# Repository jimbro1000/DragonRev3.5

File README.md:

# DRAGON 32 CPU Rev 3(.5) #

This project contains the design for a hugely upgraded version
of the Dragon 32 (technically a Dragon 64 for pedants)

The basis of the design is the Dragon 32 recreation that I have
been refining for some time. The peripheral IO remains as originally
specified by Dragon Data but the ram, address multiplexer and video
display generator or implemented on a separate plug-in component.

Technically the original ICs could be implemented on the plug-in and
you would be left with an original piece of hardware (in terms of
function). I already have a board for that though...

The benefit of the plugin board is to implement the complex (and
expensive) fabrication on a smaller device and abstract away the
upgrades that are contained.

Almost every passive component and supporting logic ICs have been
switched to surface mount technology. This means the board can be
part assembled at relatively low cost, leaving just the major ICs,
ports, connectors and relay to be hand assembled.

## Core Design ##
### Main Board ###

The main board replicates the footprint of the original D64 PCB.
Ports and fixings are all in their original positions.

The CPU lives on the main board with any speed variant supported
including the HD63C09. The onboard ROM is integrated into a single 
chip holding both banks of the D64 ROM image.

All IO (except video) is performed by the original hardware so the 
two PIAs and UART are retained.

The device select signals for peripherals has been disambiguated
from two devices which repeat the same four addresses eight times, 
to sixteen devices, each with four mapped addresses.

* $FF00-$FF03 (P0a) is still the original PIA0
* $FF04-$FF07 (P0b) is the original UART
* $FF20-$FF23 (P1a) is still the original PIA1

These three blocks maintain compatibility with the original ROM
software.

The other blocks (P0c-P0g and P1b-P1g) are unused and can be
adopted for other hardware (see audio)

### Core Board ###

The core board provides RAM, Video and SAM functionality. The
minimum version of this would be the original RAM, VDG and SAM
chips which effectively reproduces the original D64 specification.

At this time two upgrade core boards exist. The first is a mild
upgrade that provides 2MB of RAM, a SAMx implementation and an
upgraded VDG that replicates the video functionality of the 
CoCo3 GIME chip

The second core board provides all of the capabilities of the
first board but adds a soft 6809 CPU that can operate alongside
or instead of the CPU on the main board. This second CPU can
operate at much higher speeds than the original, match the
speed of the original or be completely disabled. When both
CPUs are operating the second CPU can be completely detached
from everything except RAM and running on an independent
clock cycle, or it can share the full bus with the hardware
CPU utilising the bus mastering signals.

The second core also introduces a DMA capability that enables
very fast memory copy actions, running independently of either
CPU.

The video capabilities of the second core add sprite handling
and tile based video modes, all in a layered video system that
allows tiles, bitmaps and sprites to exist on the same display.

For details of the core implementations see the separate
hardware and firmware repositories.

### Audio Board ###

The main board will (but does not currently) provide a socket
for an audio upgrade. The proposal is to utilise four or six
peripheral address blocks to provide an interface to the audio
board. Each block effectively represents a single audio device.

The multi device approach should allow the audio board to 
generate a rich stereo output with multiple audio waveforms
per stereo channel.

Optionally I want to look at live mixing of the audio to allow
user selection of which waveform ends up on which channel. This
would likely consume another peripheral address block.

Following this approach would permit the use of original sound
generator chips but has the problem of identifying the source
of interrupts.

An alternative is to define a soft audio generator in a MCU
or CPLD that focuses all of the IO into a single hardware
device (possibly still using multiple peripheral IO blocks)
but potentially makes the hardware interface non-standard.
If a suitable open source firmware definition can be
identified, this is likely to be the better option.

An example of this would be the [YM2149 PSG System](https://github.com/nockieboy/YM2149_PSG_system)
that implements a simulation of dual YM2149s (or 
AY-3-8910s) with stereo mixer and bass and treble controls.

Due to the limited external IO required this could be implemeted
on a relatively cheap, modest FPGA device rather than the main core
board which requires a significant level of IO connectivity.

## Modifications ##
### Joysticks ###

The two joystick ports provide a second fire button capability
wired to consecutive keyboard rows, as per the Tandy CoCo. 
Unless a two button joystick is used this make no difference to
the operation of the computer. It also requires the use of 6-pin 
DIN sockets, these are pin compatible with the 5-pin originals
so a regular single button joystick can still be used.

The two extra buttons can also be disabled by omitting L3 and L4

## License

This project and all its hardware design are licensed under
creative commons [CC BY-NC 4.0](https://creativecommons.org/licenses/by-nc/4.0/deed.en)

__You are free to:__

Share - copy and redistribute the material in any medium or format

Adapt - remix, transform, and build upon the material

The licensor cannot revoke these freedoms as long as you follow the 
license terms.

__Under the following terms:__

Attribution - You must give appropriate credit, provide a link to the 
license, and indicate if changes were made. You may do so in any 
reasonable manner, but not in any way that suggests the licensor 
endorses you or your use.

NonCommercial - You may not use the material for commercial purposes.

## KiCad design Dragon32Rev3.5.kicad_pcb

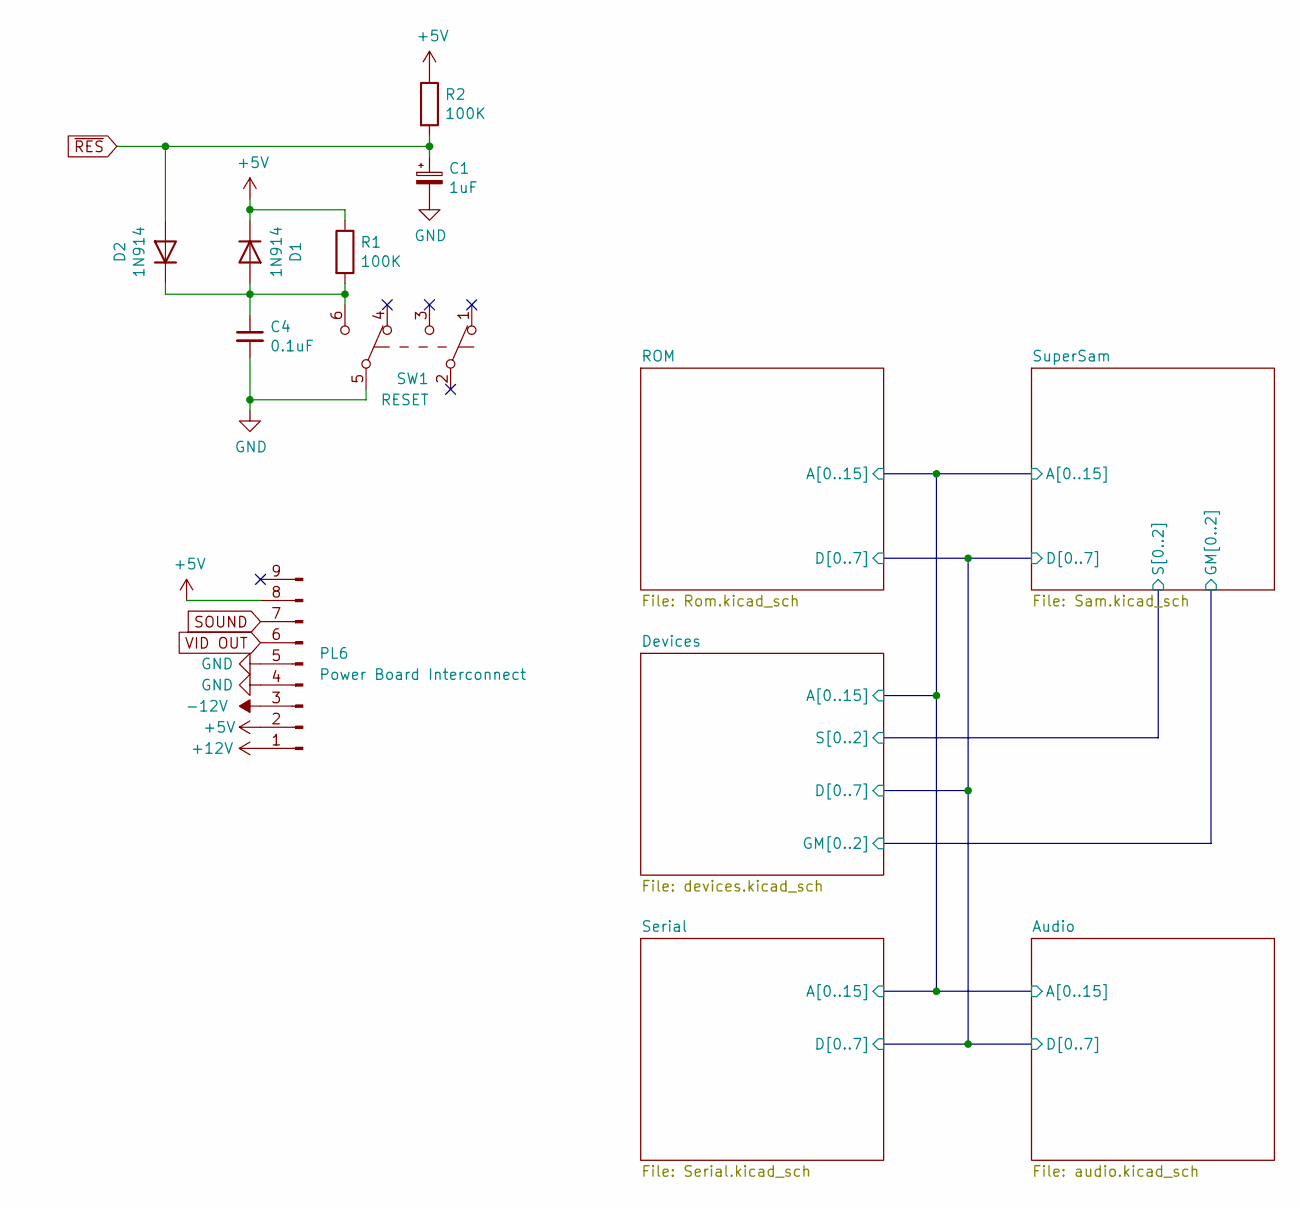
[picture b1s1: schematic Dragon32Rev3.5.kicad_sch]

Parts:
C1: 1uF; CP_Elec_4x4.5; DigiKey 732-8541-1-ND
C4: 0.1uF; C_0805_2012Metric; DigiKey C0805F104K1RACAUTO
D1, D2: 1N914; D_SOD-523; DigiKey 1N914BWTCT-ND
PL6: Power Board Interconnect; Molex_KK-396_A-41791-0009_1x09_P3.96mm_Vertical; DigiKey 2057-LHD-09-TS-ND
R1, R2: 100K; R_0402_1005Metric; DigiKey YAG2304CT-ND
SW1: RESET; Button_AlpsAlpine_SPUN190900; DigiKey 401-1225-ND

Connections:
+5V: D1.1 (K), PL6.2, PL6.8, R1.1, R2.1; also elsewhere on the board
+12V: PL6.1; also elsewhere on the board
-12V: PL6.3; also elsewhere on the board
GND: C1.2, C4.2, PL6.4, PL6.5, SW1.5 (B); also elsewhere on the board
unnamed: C4.1, D1.2 (A), D2.1 (K), R1.2, SW1.6 (C)
SOUND: PL6.7; also elsewhere on the board
VID OUT: PL6.6; also elsewhere on the board
~RES: C1.1, D2.2 (A), R2.2

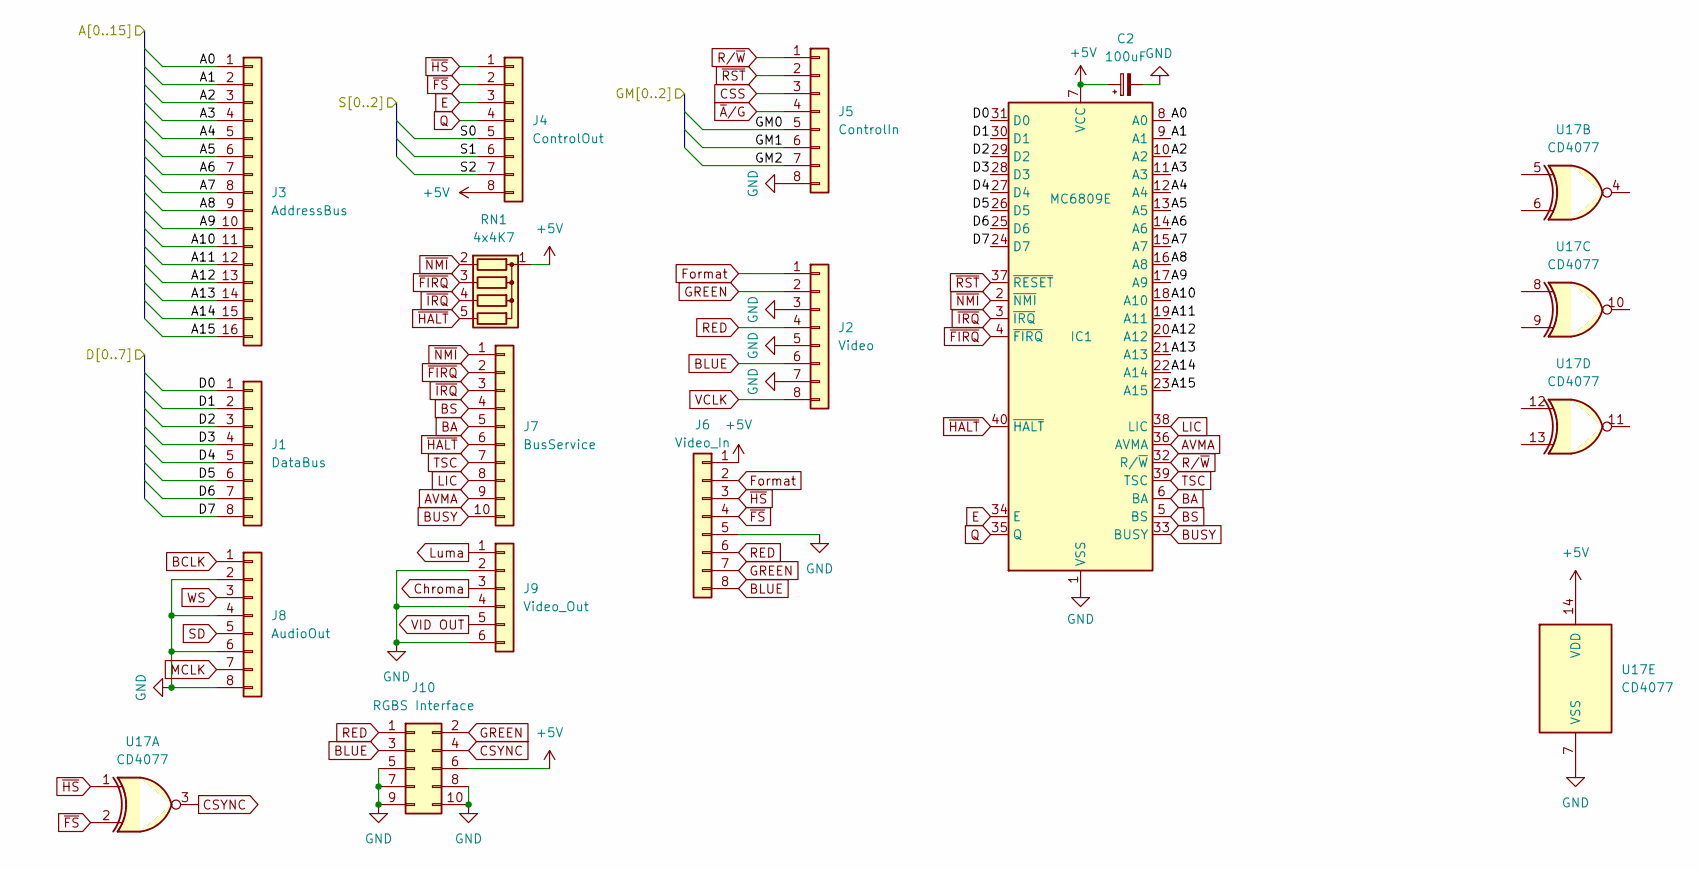
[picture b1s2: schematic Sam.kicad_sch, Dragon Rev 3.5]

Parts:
C2: 100uF; CP_Elec_5x5.3; DigiKey 732-6410-1-ND
IC1: MC6809E; DIP-40_W15.24mm; Mouser 517-4840-6000-CP
J1: DataBus; PinHeader_1x08_P2.54mm_Vertical
J2: Video; PinHeader_1x08_P2.54mm_Vertical
J3: AddressBus; PinHeader_1x16_P2.54mm_Vertical
J4: ControlOut; PinHeader_1x08_P2.54mm_Vertical
J5: ControlIn; PinHeader_1x08_P2.54mm_Vertical
J6: Video_In; PinHeader_1x08_P2.54mm_Vertical
J7: BusService; PinHeader_1x10_P2.54mm_Vertical
J8: AudioOut; PinHeader_1x08_P2.54mm_Vertical
J9: Video_Out; PinHeader_1x06_P2.54mm_Vertical
J10: RGBS Interface; IDC-Header_2x05_P2.54mm_Vertical
RN1: 4x4K7; R_Array_SIP5
U17: CD4077; SOIC-16_3.9x9.9mm_P1.27mm; DigiKey 296-31521-1-ND

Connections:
+5V: C2.1, IC1.7 (VCC), J4.8, J6.1, J10.6, RN1.1 (common), U17.14 (VDD); also elsewhere on the board
/Audio/A0: IC1.8 (A0), J3.1; also elsewhere on the board
/Audio/A1: IC1.9 (A1), J3.2; also elsewhere on the board
/Audio/A2: IC1.10 (A2), J3.3; also elsewhere on the board
/Audio/A3: IC1.11 (A3), J3.4; also elsewhere on the board
/Audio/A4: IC1.12 (A4), J3.5; also elsewhere on the board
/Audio/A5: IC1.13 (A5), J3.6; also elsewhere on the board
/Audio/A6: IC1.14 (A6), J3.7; also elsewhere on the board
/Audio/A7: IC1.15 (A7), J3.8; also elsewhere on the board
/Audio/A8: IC1.16 (A8), J3.9; also elsewhere on the board
/Audio/A9: IC1.17 (A9), J3.10; also elsewhere on the board
/Audio/A10: IC1.18 (A10), J3.11; also elsewhere on the board
/Audio/A11: IC1.19 (A11), J3.12; also elsewhere on the board
/Audio/A12: IC1.20 (A12), J3.13; also elsewhere on the board
/Audio/A13: IC1.21 (A13), J3.14; also elsewhere on the board
/Audio/A14: IC1.22 (A14), J3.15; also elsewhere on the board
/Audio/A15: IC1.23 (A15), J3.16; also elsewhere on the board
/Audio/D0: IC1.31 (D0), J1.1; also elsewhere on the board
/Audio/D1: IC1.30 (D1), J1.2; also elsewhere on the board
/Audio/D2: IC1.29 (D2), J1.3; also elsewhere on the board
/Audio/D3: IC1.28 (D3), J1.4; also elsewhere on the board
/Audio/D4: IC1.27 (D4), J1.5; also elsewhere on the board
/Audio/D5: IC1.26 (D5), J1.6; also elsewhere on the board
/Audio/D6: IC1.25 (D6), J1.7; also elsewhere on the board
/Audio/D7: IC1.24 (D7), J1.8; also elsewhere on the board
/Devices/GM0: J5.5; also elsewhere on the board
/Devices/GM1: J5.6; also elsewhere on the board
/Devices/GM2: J5.7; also elsewhere on the board
/Devices/S0: J4.5; also elsewhere on the board
/Devices/S1: J4.6; also elsewhere on the board
/Devices/S2: J4.7; also elsewhere on the board
AVMA: IC1.36 (AVMA), J7.9
BA: IC1.6 (BA), J7.5
BCLK: J8.1; also elsewhere on the board
BLUE: J2.6, J6.8, J10.3
BS: IC1.5 (BS), J7.4
BUSY: IC1.33 (BUSY), J7.10
CSS: J5.3; also elsewhere on the board
CSYNC: J10.4, U17.3
Chroma: J9.3
E: IC1.34 (E), J4.3; also elsewhere on the board
Format: J2.1, J6.2
GND: C2.2, IC1.1 (VSS), J2.3, J2.5, J2.7, J5.8, J6.5, J8.2, J8.4, J8.6, J8.8, J9.2, J9.4, J9.6, J10.5, J10.7, J10.8, J10.9, J10.10, U17.7 (VSS); also elsewhere on the board
GREEN: J2.2, J6.7, J10.2
LIC: IC1.38 (LIC), J7.8
Luma: J9.1
MCLK: J8.7; also elsewhere on the board
Q: IC1.35 (Q), J4.4; also elsewhere on the board
RED: J2.4, J6.6, J10.1
R/~W: IC1.32 (R/~W), J5.1; also elsewhere on the board
SD: J8.5; also elsewhere on the board
TSC: IC1.39 (TSC), J7.7
VCLK: J2.8; also elsewhere on the board
VID OUT: J9.5; also elsewhere on the board
WS: J8.3; also elsewhere on the board
~A/G: J5.4; also elsewhere on the board
~FIRQ: IC1.4 (~FIRQ), J7.2, RN1.3 (R2); also elsewhere on the board
~FS: J4.2, J6.4, U17.2; also elsewhere on the board
~HALT: IC1.40 (~HALT), J7.6, RN1.5 (R4); also elsewhere on the board
~HS: J4.1, J6.3, U17.1
~IRQ: IC1.3 (~IRQ), J7.3, RN1.4 (R3); also elsewhere on the board
~NMI: IC1.2 (~NMI), J7.1, RN1.2 (R1); also elsewhere on the board
~RST: IC1.37 (~RESET), J5.2; also elsewhere on the board

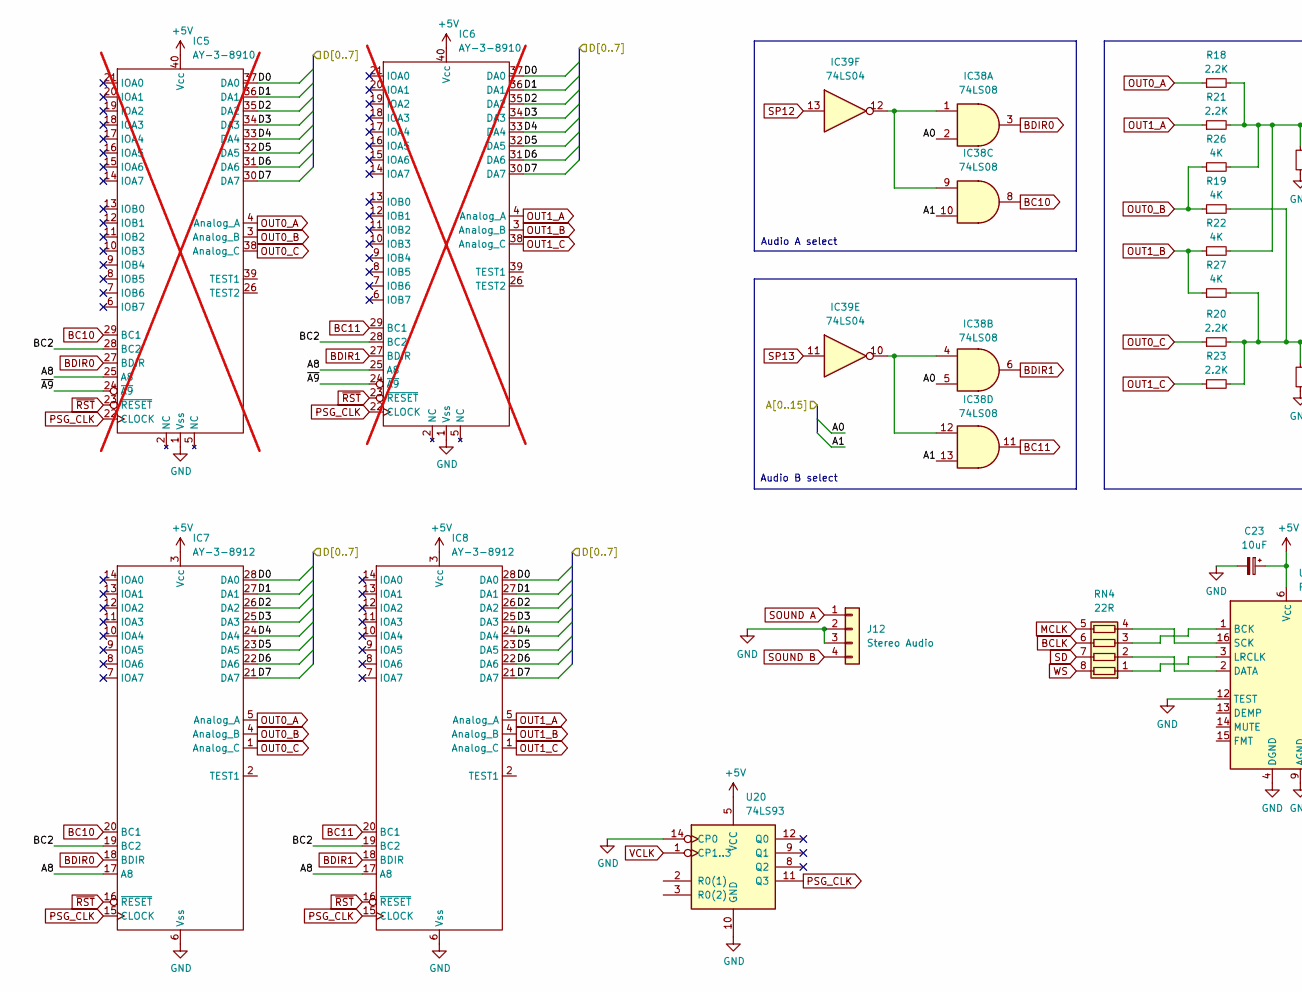
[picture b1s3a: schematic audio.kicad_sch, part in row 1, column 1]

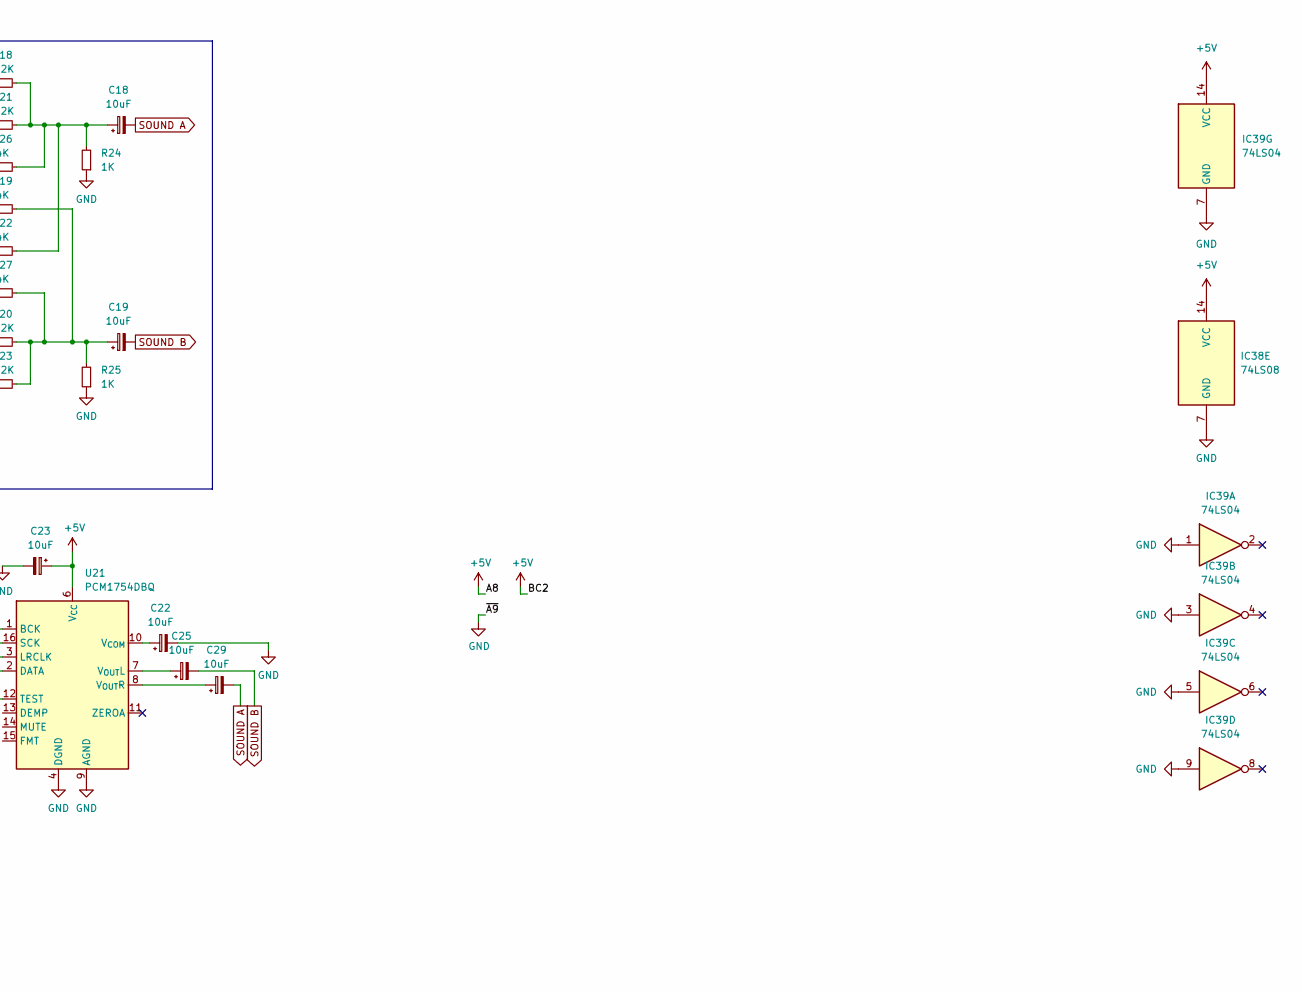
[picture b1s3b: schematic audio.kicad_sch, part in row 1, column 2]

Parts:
C18, C19, C22, C23, C25, C29: 10uF; CP_Elec_4x3
IC5, IC6: AY-3-8910; DIP-40_W15.24mm_Socket; not fitted
IC7, IC8: AY-3-8912; DIP-28_W15.24mm_Socket
IC38: 74LS08; SOIC-14_3.9x8.7mm_P1.27mm; LCSC C22394768
IC39: 74LS04; SOIC-14_3.9x8.7mm_P1.27mm; LCSC C22374093
J12: Stereo Audio; JST_EH_S4B-EH_1x04_P2.50mm_Horizontal
R18, R20, R21, R23: 2.2K; R_0603_1608Metric
R19, R22, R26, R27: 4K; R_0603_1608Metric
R24, R25: 1K; R_0603_1608Metric
RN4: 22R; R_Array_Convex_4x0603
U20: 74LS93; SOIC-14_3.9x8.7mm_P1.27mm
U21: PCM1754DBQ; SSOP-16_3.9x4.9mm_P0.635mm

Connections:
+5V: C23.1, IC5.25 (A8), IC5.28 (BC2), IC5.40 (Vcc), IC6.25 (A8), IC6.28 (BC2), IC6.40 (Vcc), IC7.3 (Vcc), IC7.17 (A8), IC7.19 (BC2), IC8.3 (Vcc), IC8.17 (A8), IC8.19 (BC2), IC38.14 (VCC), IC39.14 (VCC), U20.5 (VCC), U21.6 (V_{CC}); also elsewhere on the board
/Audio/A0: IC38.2, IC38.5; also elsewhere on the board
/Audio/A1: IC38.10, IC38.13; also elsewhere on the board
/Audio/D0: IC5.37 (DA0), IC6.37 (DA0), IC7.28 (DA0), IC8.28 (DA0); also elsewhere on the board
/Audio/D1: IC5.36 (DA1), IC6.36 (DA1), IC7.27 (DA1), IC8.27 (DA1); also elsewhere on the board
/Audio/D2: IC5.35 (DA2), IC6.35 (DA2), IC7.26 (DA2), IC8.26 (DA2); also elsewhere on the board
/Audio/D3: IC5.34 (DA3), IC6.34 (DA3), IC7.25 (DA3), IC8.25 (DA3); also elsewhere on the board
/Audio/D4: IC5.33 (DA4), IC6.33 (DA4), IC7.24 (DA4), IC8.24 (DA4); also elsewhere on the board
/Audio/D5: IC5.32 (DA5), IC6.32 (DA5), IC7.23 (DA5), IC8.23 (DA5); also elsewhere on the board
/Audio/D6: IC5.31 (DA6), IC6.31 (DA6), IC7.22 (DA6), IC8.22 (DA6); also elsewhere on the board
/Audio/D7: IC5.30 (DA7), IC6.30 (DA7), IC7.21 (DA7), IC8.21 (DA7); also elsewhere on the board
BC10: IC5.29 (BC1), IC7.20 (BC1), IC38.8
BC11: IC6.29 (BC1), IC8.20 (BC1), IC38.11
BCLK: RN4.6 (R3.2); also elsewhere on the board
BDIR0: IC5.27 (BDIR), IC7.18 (BDIR), IC38.3
BDIR1: IC6.27 (BDIR), IC8.18 (BDIR), IC38.6
GND: C22.2, C23.2, IC5.1 (Vss), IC5.24 (~A9), IC6.1 (Vss), IC6.24 (~A9), IC7.6 (Vss), IC8.6 (Vss), IC38.7 (GND), IC39.1, IC39.3, IC39.5, IC39.7 (GND), IC39.9, J12.2, J12.3, R24.1, R25.1, U20.10 (GND), U20.14 (CP0), U21.4 (DGND), U21.9 (AGND), U21.12 (TEST); also elsewhere on the board
MCLK: RN4.5 (R4.2); also elsewhere on the board
unnamed: C18.1, R18.2, R21.2, R22.2, R24.2, R26.2
unnamed: C19.1, R19.2, R20.2, R23.2, R25.2, R27.2
unnamed: IC38.1, IC38.9, IC39.12
unnamed: IC38.4, IC38.12, IC39.10
unnamed: RN4.1 (R1.1), U21.3 (LRCLK)
unnamed: RN4.2 (R2.1), U21.2 (DATA)
unnamed: RN4.3 (R3.1), U21.1 (BCK)
unnamed: RN4.4 (R4.1), U21.16 (SCK)
unnamed: C22.1, U21.10 (V_{COM})
unnamed: C25.1, U21.7 (V_{OUT}L)
unnamed: C29.1, U21.8 (V_{OUT}R)
OUT0_A: IC5.4 (Analog_A), IC7.5 (Analog_A), R18.1
OUT0_B: IC5.3 (Analog_B), IC7.4 (Analog_B), R19.1, R26.1
OUT0_C: IC5.38 (Analog_C), IC7.1 (Analog_C), R20.1
OUT1_A: IC6.4 (Analog_A), IC8.5 (Analog_A), R21.1
OUT1_B: IC6.3 (Analog_B), IC8.4 (Analog_B), R22.1, R27.1
OUT1_C: IC6.38 (Analog_C), IC8.1 (Analog_C), R23.1
PSG_CLK: IC5.22 (CLOCK), IC6.22 (CLOCK), IC7.15 (CLOCK), IC8.15 (CLOCK), U20.11 (Q3)
SD: RN4.7 (R2.2); also elsewhere on the board
SOUND A: C18.2, C29.2, J12.1
SOUND B: C19.2, C25.2, J12.4
SP12: IC39.13; also elsewhere on the board
SP13: IC39.11; also elsewhere on the board
VCLK: U20.1 (CP1..3); also elsewhere on the board
WS: RN4.8 (R1.2); also elsewhere on the board
~RST: IC5.23 (~RESET), IC6.23 (~RESET), IC7.16 (~RESET), IC8.16 (~RESET); also elsewhere on the board

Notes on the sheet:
Audio B select
Audio A select

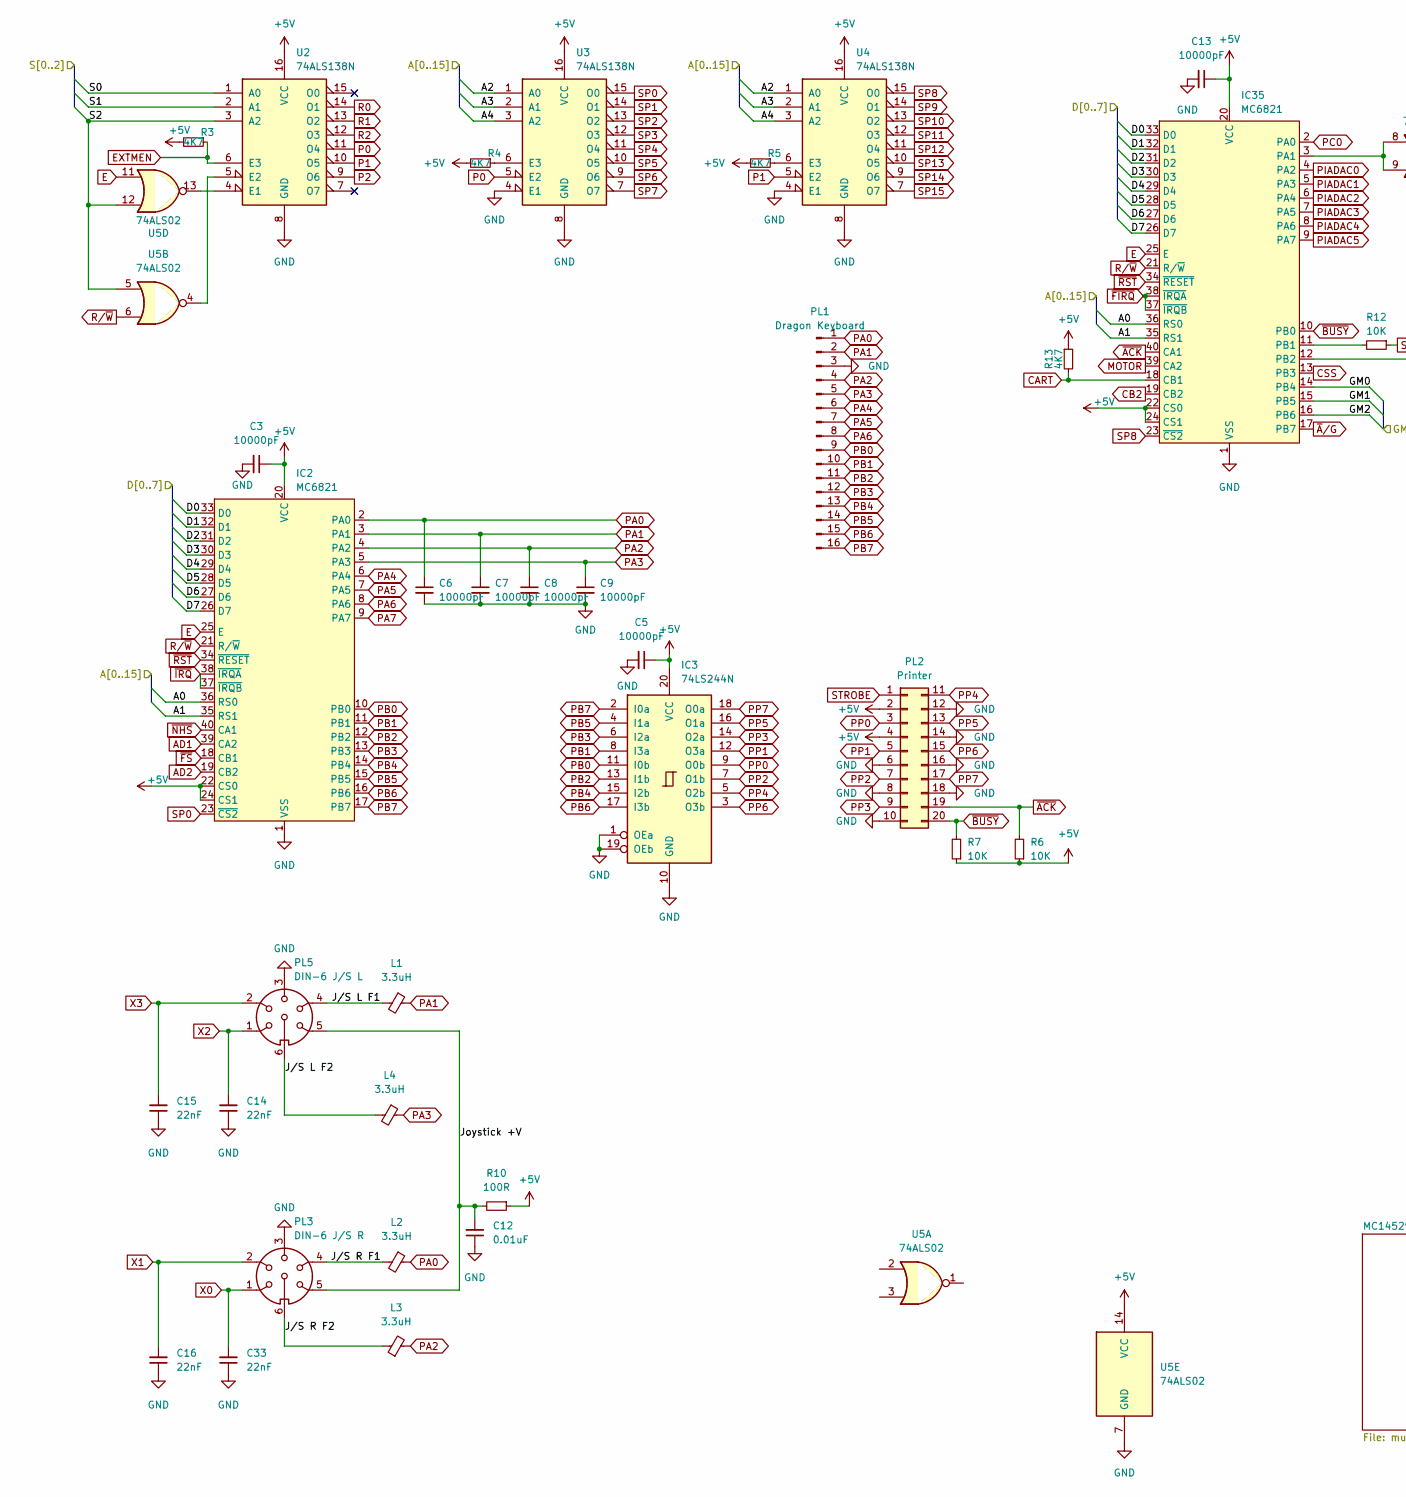
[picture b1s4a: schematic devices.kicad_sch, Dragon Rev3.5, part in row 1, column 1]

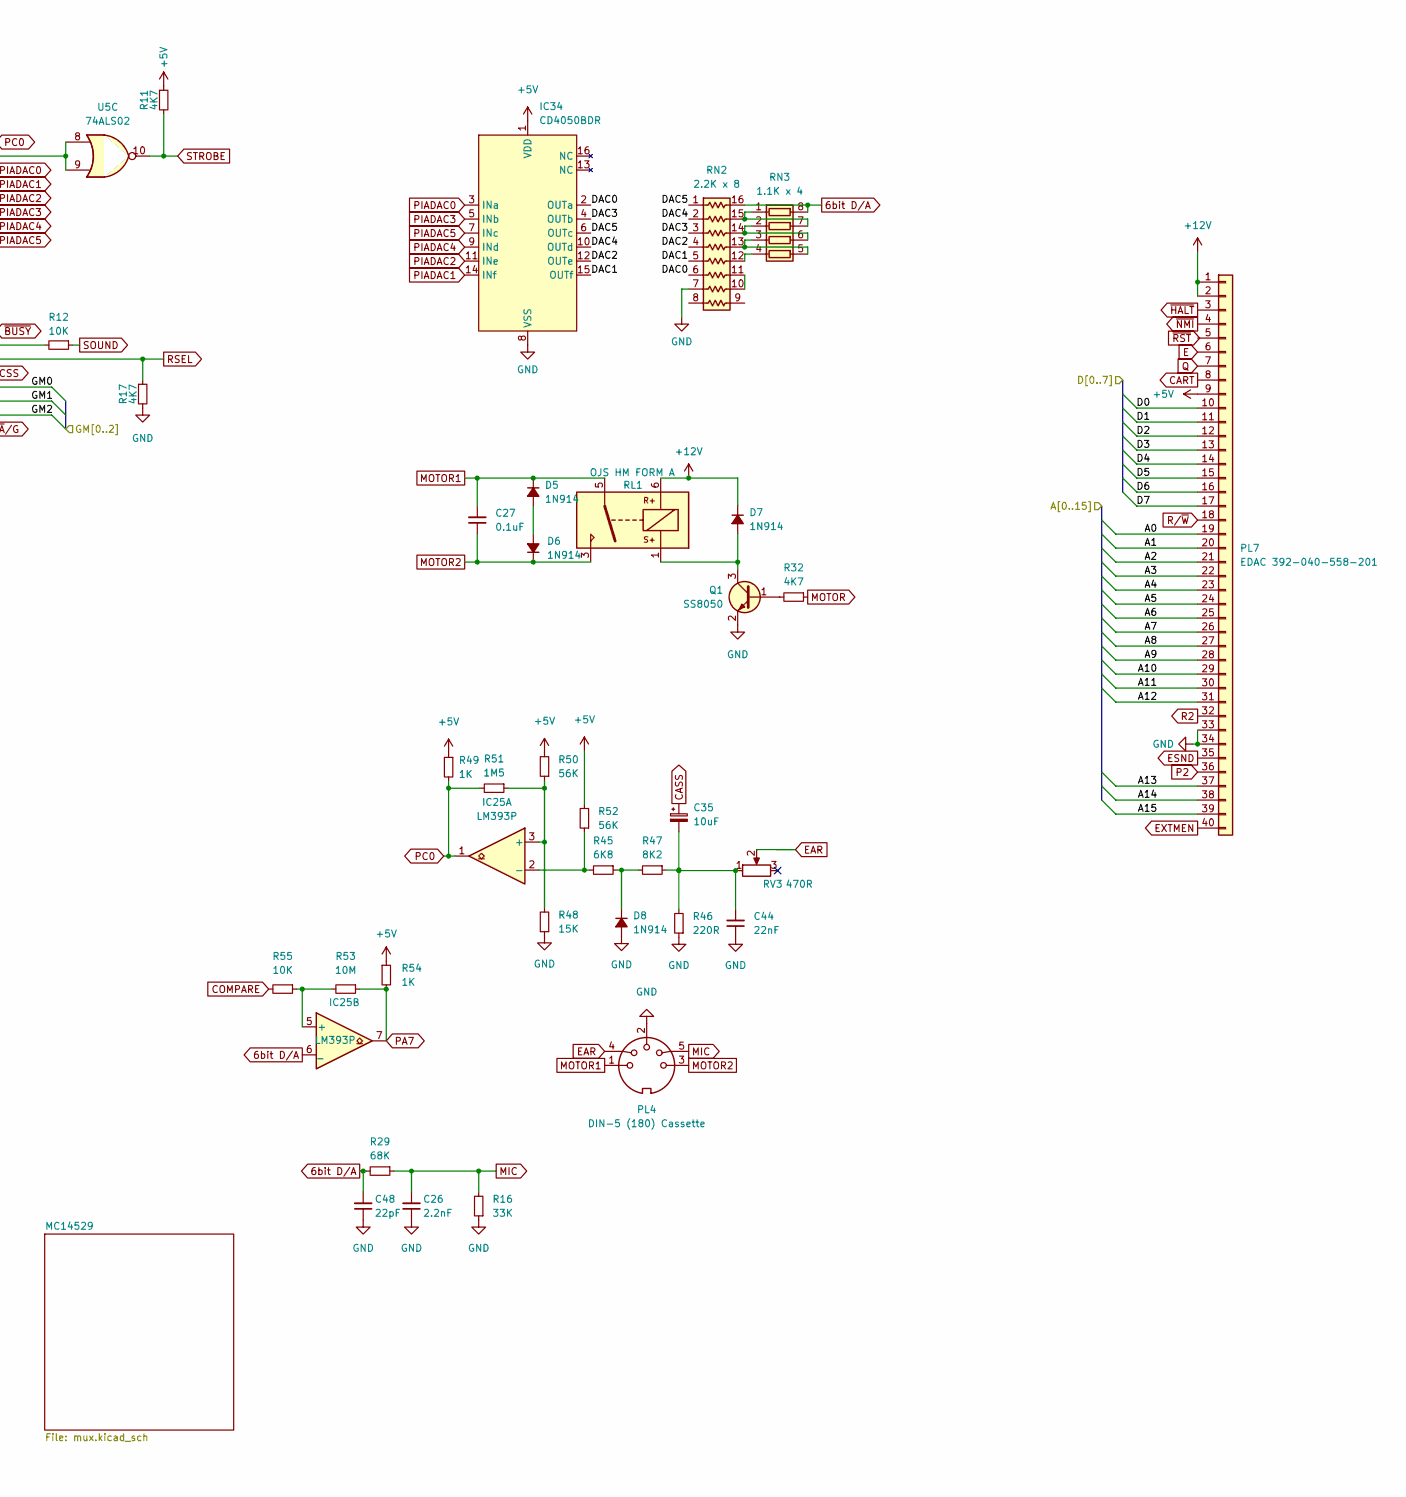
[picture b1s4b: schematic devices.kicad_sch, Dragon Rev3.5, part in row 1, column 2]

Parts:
C3, C5, C6, C7, C8, C9, C13: 10000pF; C_0603_1608Metric; DigiKey 399-C0603C103K5RACTUCT-ND
C12: 0.01uF; C_0603_1608Metric; DigiKey BC2662CT-ND
C14, C15, C16, C33: 22nF; C_0603_1608Metric; DigiKey 1276-CL10B223KO8WPNCCT-ND
C26: 2.2nF; C_0603_1608Metric; DigiKey 399-C0603C222K4RECAUTOCT-ND
C27: 0.1uF; C_0805_2012Metric; DigiKey C0805F104K1RACAUTO
C35: 10uF; CP_EIA-3528-21_Kemet-B; DigiKey 478-5257-1-ND
C44: 22nF; C_0603_1608Metric; DigiKey BC2677CT-ND
C48: 22pF; C_0603_1608Metric; DigiKey 478-KGM15ACG1C220KTCT-ND
D5, D6, D7, D8: 1N914; D_SOD-523; DigiKey 1N914FS-ND
IC2, IC35: MC6821; DIP-40_W15.24mm; Mouser 517-4840-6000-CP
IC3: 74LS244N; SOIC-20W_7.5x12.8mm_P1.27mm; DigiKey 296-1213-1-ND
IC25: LM393P; TSSOP-8_4.4x3mm_P0.65mm; DigiKey 497-7333-1-ND
IC34: CD4050BDR; SOIC-16_3.9x9.9mm_P1.27mm; DigiKey 296-31503-1-ND
L1, L2, L3, L4: 3.3uH; L_0805_2012Metric; DigiKey 445-15749-1-ND
PL1: Dragon Keyboard; PinHeader_1x16_P2.54mm_Vertical; DigiKey 952-2521-ND
PL2: Printer; IDC-Header_2x10-1MP_P2.54mm_Latch_Horizontal; DigiKey CHR20G-ND
PL3: DIN-6 J/S R; DIN-6_DELTRON_671-0601_Horizontal; DigiKey CP-7060-ND
PL4: DIN-5 (180) Cassette; DIN-5_DELTRON_671-0501_45deg_Horizontal; DigiKey CP-7050-ND
PL5: DIN-6 J/S L; DIN-6_DELTRON_671-0601_Horizontal; DigiKey CP-7060-ND
PL7: EDAC 392-040-558-201; Edge_2x20_P2.54mm_OvalMP; DigiKey 151-342-040-558-201-ND
Q1: SS8050; SOT-23-3; DigiKey 641-1790-1-ND
R3, R4, R5, R11, R13, R17: 4K7; R_0402_1005Metric; DigiKey YAG1446CT-ND
R6, R7, R12: 10K; R_0603_1608Metric; DigiKey RNCP0603FTD10K0CT-ND
R10: 100R; R_1206_3216Metric; DigiKey RNCP1206FTD100RCT-ND
R16: 33K; R_0603_1608Metric; DigiKey P33KDBCT-ND
R29: 68K; R_0805_2012Metric; DigiKey 10-ERA-6VEB6802VCT-ND
R32: 4K7; R_0402_1005Metric; DigiKey CF14JT4K70CT-ND
R45: 6K8; R_0603_1608Metric; DigiKey YAG5968CT-ND
R46: 220R; R_0603_1608Metric; DigiKey YAG1587CT-ND
R47: 8K2; R_0603_1608Metric; DigiKey MCT0603-8.20K-CFCT-ND
R48: 15K; R_0603_1608Metric; DigiKey P15KDBCT-ND
R49, R54: 1K; R_0603_1608Metric; DigiKey RNCP0603FTD1K00CT-ND
R50: 56K; R_0603_1608Metric; DigiKey P56KDBCT-ND
R51: 1M5; R_0805_2012Metric; DigiKey CF14JT1M50CT-ND
R52: 56K; R_0603_1608Metric; DigiKey 13-RT0603FRE0756KLCT-ND
R53: 10M; R_1206_3216Metric; DigiKey 749-MCA1206MD1005BP100CT-ND
R55: 10K; R_0805_2012Metric; DigiKey RG20P10.0KBCT-ND
RL1: OJS HM FORM A; OJS HM 10A Relay; DigiKey 41-OJS-SH-105HMF,00000-ND
RN2: 2.2K x 8; R_Array_Convex_8x0602; DigiKey 60-742C163222JPCT-ND
RN3: 1.1K x 4; R_Array_Convex_4x0603
RV3: 470R; Potentiometer_Bourns_3386X_Horizontal; DigiKey 3386H-103LF-ND
U2, U3, U4: 74ALS138N; SOIC-16_3.9x9.9mm_P1.27mm; DigiKey 296-14714-1-ND
U5: 74ALS02; SOIC-16_3.9x9.9mm_P1.27mm; DigiKey 296-5002-5-ND

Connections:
6bit D/A: C48.2, IC25.6 (_), R29.2, RN2.16 (R1.2), RN3.8 (R1.2); also elsewhere on the board
+5V: C3.1, C5.1, C13.1, IC2.20 (VCC), IC2.22 (CS0), IC2.24 (CS1), IC3.20 (VCC), IC34.1 (VDD), IC35.20 (VCC), IC35.22 (CS0), IC35.24 (CS1), PL2.2, PL2.4, PL7.9, R3.2, R4.2, R5.2, R6.1, R7.1, R10.1, R11.1, R13.1, R49.1, R50.2, R52.2, R54.1, U2.16 (VCC), U3.16 (VCC), U4.16 (VCC), U5.14 (VCC); also elsewhere on the board
+12V: D7.1 (K), PL7.1, PL7.2, RL1.6; also elsewhere on the board
/Audio/A0: IC2.36 (RS0), IC35.36 (RS0), PL7.19; also elsewhere on the board
/Audio/A1: IC2.35 (RS1), IC35.35 (RS1), PL7.20; also elsewhere on the board
/Audio/A2: PL7.21, U3.1 (A0), U4.1 (A0); also elsewhere on the board
/Audio/A3: PL7.22, U3.2 (A1), U4.2 (A1); also elsewhere on the board
/Audio/A4: PL7.23, U3.3 (A2), U4.3 (A2); also elsewhere on the board
/Audio/A5: PL7.24; also elsewhere on the board
/Audio/A6: PL7.25; also elsewhere on the board
/Audio/A7: PL7.26; also elsewhere on the board
/Audio/A8: PL7.27; also elsewhere on the board
/Audio/A9: PL7.28; also elsewhere on the board
/Audio/A10: PL7.29; also elsewhere on the board
/Audio/A11: PL7.30; also elsewhere on the board
/Audio/A12: PL7.31; also elsewhere on the board
/Audio/A13: PL7.37; also elsewhere on the board
/Audio/A14: PL7.38; also elsewhere on the board
/Audio/A15: PL7.39; also elsewhere on the board
/Audio/D0: IC2.33 (D0), IC35.33 (D0), PL7.10; also elsewhere on the board
/Audio/D1: IC2.32 (D1), IC35.32 (D1), PL7.11; also elsewhere on the board
/Audio/D2: IC2.31 (D2), IC35.31 (D2), PL7.12; also elsewhere on the board
/Audio/D3: IC2.30 (D3), IC35.30 (D3), PL7.13; also elsewhere on the board
/Audio/D4: IC2.29 (D4), IC35.29 (D4), PL7.14; also elsewhere on the board
/Audio/D5: IC2.28 (D5), IC35.28 (D5), PL7.15; also elsewhere on the board
/Audio/D6: IC2.27 (D6), IC35.27 (D6), PL7.16; also elsewhere on the board
/Audio/D7: IC2.26 (D7), IC35.26 (D7), PL7.17; also elsewhere on the board
/Devices/DAC0: IC34.2 (OUTa), RN2.6 (R6.1)
/Devices/DAC1: IC34.15 (OUTf), RN2.5 (R5.1)
/Devices/DAC2: IC34.12 (OUTe), RN2.4 (R4.1)
/Devices/DAC3: IC34.4 (OUTb), RN2.3 (R3.1)
/Devices/DAC4: IC34.10 (OUTd), RN2.2 (R2.1)
/Devices/DAC5: IC34.6 (OUTc), RN2.1 (R1.1)
/Devices/GM0: IC35.14 (PB4); also elsewhere on the board
/Devices/GM1: IC35.15 (PB5); also elsewhere on the board
/Devices/GM2: IC35.16 (PB6); also elsewhere on the board
/Devices/Joystick +V: C12.2, PL3.5, PL5.5, R10.2
/Devices/J/S L F1: L1.2, PL5.4
/Devices/J/S L F2: L4.2, PL5.6
/Devices/J/S R F1: L2.2, PL3.4
/Devices/J/S R F2: L3.1, PL3.6
/Devices/S0: U2.1 (A0); also elsewhere on the board
/Devices/S1: U2.2 (A1); also elsewhere on the board
/Devices/S2: U2.3 (A2), U5.5, U5.12; also elsewhere on the board
AD1: IC2.39 (CA2); also elsewhere on the board
AD2: IC2.19 (CB2); also elsewhere on the board
CART: IC35.18 (CB1), PL7.8, R13.2
CASS: C35.1; also elsewhere on the board
CB2: IC35.19 (CB2); also elsewhere on the board
COMPARE: R55.2; also elsewhere on the board
CSS: IC35.13 (PB3); also elsewhere on the board
E: IC2.25 (E), IC35.25 (E), PL7.6, U5.11; also elsewhere on the board
EAR: PL4.4, RV3.2
ESND: PL7.35; also elsewhere on the board
EXTMEN: PL7.40, R3.1, U2.6 (E3)
GND: C3.2, C5.2, C6.2, C7.2, C8.2, C9.2, C12.1, C13.2, C14.1, C15.1, C16.1, C26.1, C33.1, C44.1, C48.1, D8.2 (A), IC2.1 (VSS), IC3.1 (OEa), IC3.10 (GND), IC3.19 (OEb), IC34.8 (VSS), IC35.1 (VSS), PL1.3, PL2.6, PL2.8, PL2.10, PL2.12, PL2.14, PL2.16, PL2.18, PL3.3, PL4.2, PL5.3, PL7.33, PL7.34, Q1.2 (E), R16.1, R17.2, R46.1, R48.1, RN2.7 (R7.1), U2.8 (GND), U3.4 (E1), U3.8 (GND), U4.4 (E1), U4.8 (GND), U5.7 (GND); also elsewhere on the board
MIC: C26.2, PL4.5, R16.2, R29.1
MOTOR: IC35.39 (CA2), R32.1
MOTOR1: C27.2, D5.1 (K), PL4.1, RL1.5
MOTOR2: C27.1, D6.1 (K), PL4.3, RL1.3
unnamed: C35.2, C44.2, R46.2, R47.1, RV3.1
unnamed: D5.2 (A), D6.2 (A)
unnamed: D7.2 (A), Q1.3 (C), RL1.1
unnamed: D8.1 (K), R45.1, R47.2
unnamed: IC25.3 (+), R48.2, R50.1, R51.1
unnamed: IC25.2 (-), R45.2, R52.1
unnamed: IC25.5 (+), R53.2, R55.1
unnamed: IC35.3 (PA1), U5.8, U5.9
unnamed: IC35.11 (PB1), R12.2
unnamed: Q1.1 (B), R32.2
unnamed: RN2.15 (R2.2), RN3.1 (R1.1), RN3.7 (R2.2)
unnamed: RN2.14 (R3.2), RN3.2 (R2.1), RN3.6 (R3.2)
unnamed: RN2.13 (R4.2), RN3.3 (R3.1), RN3.5 (R4.2)
unnamed: RN2.12 (R5.2), RN3.4 (R4.1)
unnamed: RN2.10 (R7.2), RN2.11 (R6.2)
unnamed: U2.4 (E1), U5.13
unnamed: U2.5 (E2), U5.4
unnamed: R4.1, U3.6 (E3)
unnamed: R5.1, U4.6 (E3)
P0: U2.11 (O4), U3.5 (E2)
P1: U2.10 (O5), U4.5 (E2)
P2: PL7.36, U2.9 (O6)
PA0: C6.1, IC2.2 (PA0), L2.1, PL1.1
PA1: C7.1, IC2.3 (PA1), L1.1, PL1.2
PA2: C8.1, IC2.4 (PA2), L3.2, PL1.4
PA3: C9.1, IC2.5 (PA3), L4.1, PL1.5
PA4: IC2.6 (PA4), PL1.6
PA5: IC2.7 (PA5), PL1.7
PA6: IC2.8 (PA6), PL1.8
PA7: IC2.9 (PA7), IC25.7, R53.1, R54.2
PB0: IC2.10 (PB0), IC3.11 (I0b), PL1.9
PB1: IC2.11 (PB1), IC3.8 (I3a), PL1.10
PB2: IC2.12 (PB2), IC3.13 (I1b), PL1.11
PB3: IC2.13 (PB3), IC3.6 (I2a), PL1.12
PB4: IC2.14 (PB4), IC3.15 (I2b), PL1.13
PB5: IC2.15 (PB5), IC3.4 (I1a), PL1.14
PB6: IC2.16 (PB6), IC3.17 (I3b), PL1.15
PB7: IC2.17 (PB7), IC3.2 (I0a), PL1.16
PC0: IC25.1, IC35.2 (PA0), R49.2, R51.2
PIADAC0: IC34.3 (INa), IC35.4 (PA2)
PIADAC1: IC34.14 (INf), IC35.5 (PA3)
PIADAC2: IC34.11 (INe), IC35.6 (PA4)
PIADAC3: IC34.5 (INb), IC35.7 (PA5)
PIADAC4: IC34.9 (INd), IC35.8 (PA6)
PIADAC5: IC34.7 (INc), IC35.9 (PA7)
PP0: IC3.9 (O0b), PL2.3
PP1: IC3.12 (O3a), PL2.5
PP2: IC3.7 (O1b), PL2.7
PP3: IC3.14 (O2a), PL2.9
PP4: IC3.5 (O2b), PL2.11
PP5: IC3.16 (O1a), PL2.13
PP6: IC3.3 (O3b), PL2.15
PP7: IC3.18 (O0a), PL2.17
Q: PL7.7; also elsewhere on the board
R0: U2.14 (O1); also elsewhere on the board
R1: U2.13 (O2); also elsewhere on the board
R2: PL7.32, U2.12 (O3)
RSEL: IC35.12 (PB2), R17.1; also elsewhere on the board
R/~W: IC2.21 (R/~W), IC35.21 (R/~W), PL7.18, U5.6; also elsewhere on the board
SOUND: R12.1; also elsewhere on the board
SP0: IC2.23 (~CS2), U3.15 (O0)
SP1: U3.14 (O1); also elsewhere on the board
SP2: U3.13 (O2)
SP3: U3.12 (O3)
SP4: U3.11 (O4)
SP5: U3.10 (O5)
SP6: U3.9 (O6)
SP7: U3.7 (O7)
SP8: IC35.23 (~CS2), U4.15 (O0)
SP9: U4.14 (O1)
SP10: U4.13 (O2)
SP11: U4.12 (O3)
SP12: U4.11 (O4); also elsewhere on the board
SP13: U4.10 (O5); also elsewhere on the board
SP14: U4.9 (O6)
SP15: U4.7 (O7)
STROBE: PL2.1, R11.2, U5.10
X0: C33.2, PL3.1; also elsewhere on the board
X1: C16.2, PL3.2; also elsewhere on the board
X2: C14.2, PL5.1; also elsewhere on the board
X3: C15.2, PL5.2; also elsewhere on the board
~ACK: IC35.40 (CA1), PL2.19, R6.2
~A/G: IC35.17 (PB7); also elsewhere on the board
~BUSY: IC35.10 (PB0), PL2.20, R7.2
~FIRQ: IC35.37 (~IRQB), IC35.38 (~IRQA); also elsewhere on the board
~FS: IC2.18 (CB1); also elsewhere on the board
~HALT: PL7.3; also elsewhere on the board
~IRQ: IC2.37 (~IRQB), IC2.38 (~IRQA); also elsewhere on the board
~NHS: IC2.40 (CA1)
~NMI: PL7.4; also elsewhere on the board
~RST: IC2.34 (~RESET), IC35.34 (~RESET); also elsewhere on the board
